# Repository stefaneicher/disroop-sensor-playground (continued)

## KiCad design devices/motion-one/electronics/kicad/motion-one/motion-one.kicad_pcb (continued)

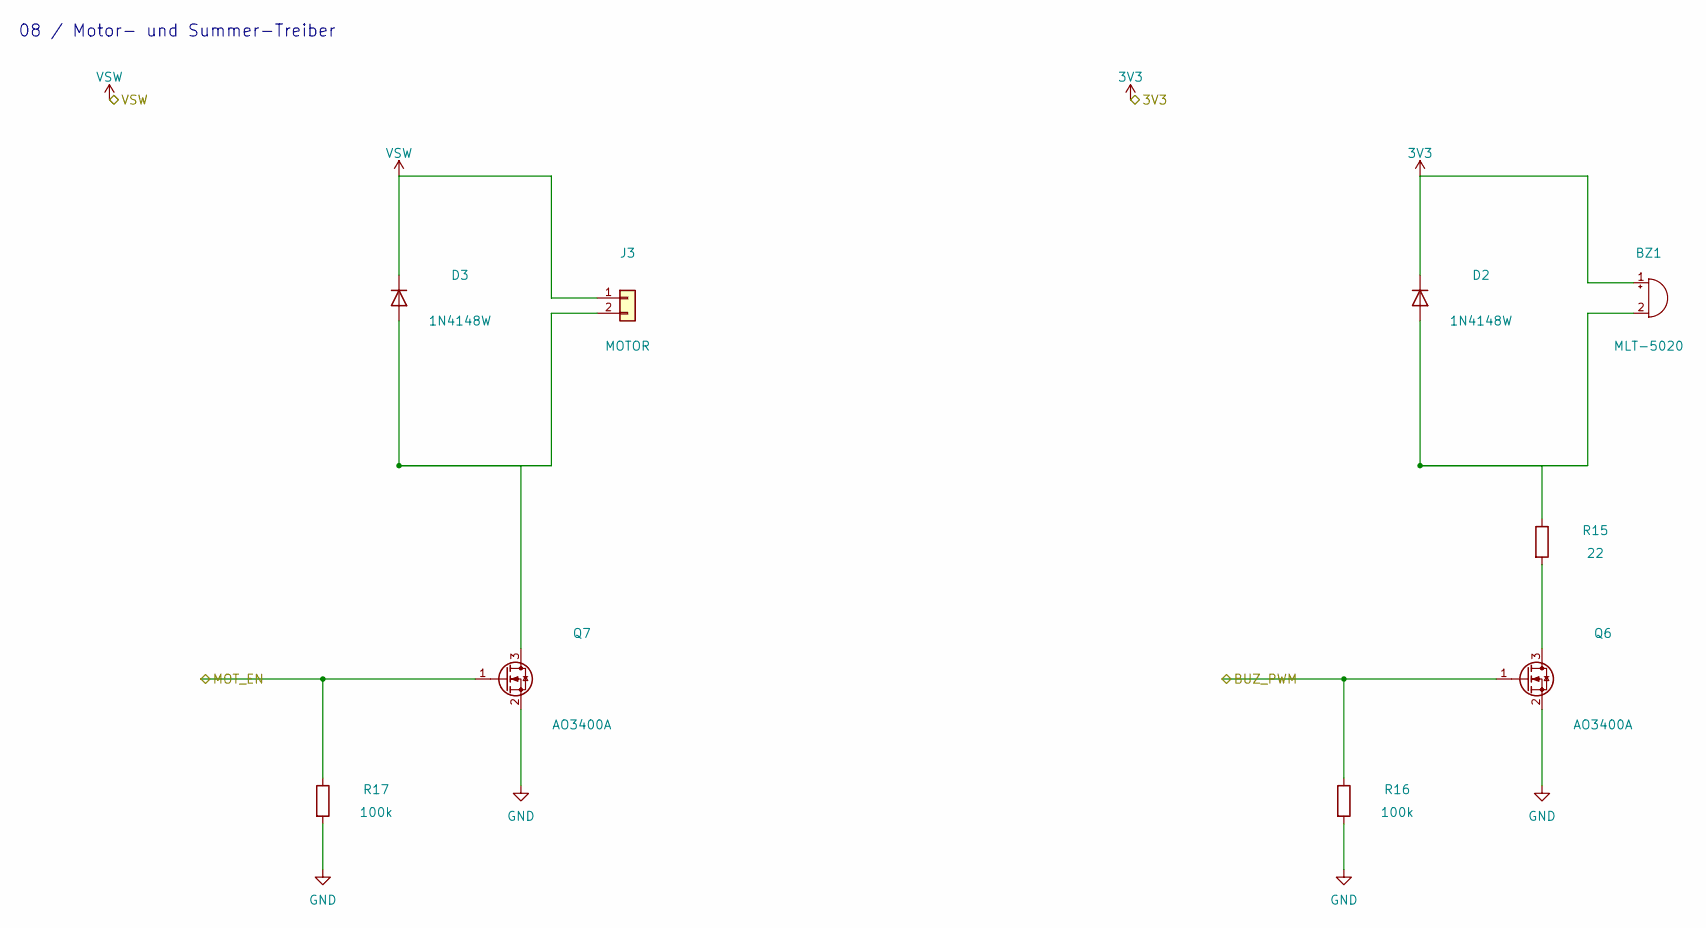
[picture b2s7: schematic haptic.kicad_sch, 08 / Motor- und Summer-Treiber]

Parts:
BZ1: MLT-5020; Buzzer_MLT-5020; LCSC C94598
D2, D3: 1N4148W; D_SOD-123; LCSC C81598
J3: MOTOR; MotorPads_2x1.5
Q6, Q7: AO3400A; SOT-23-3; LCSC C20917
R15: 22; R_1206_3216Metric; LCSC C17958
R16, R17: 100k; R_0402_1005Metric; LCSC C25741

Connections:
3V3: BZ1.1 (+), D2.1 (K); also elsewhere on the board
/haptic/BUZ_PWM: Q6.1 (G), R16.1; also elsewhere on the board
/haptic/MOT_EN: Q7.1 (G), R17.1; also elsewhere on the board
unnamed: BZ1.2 (-), D2.2 (A), R15.1
unnamed: D3.2 (A), J3.2, Q7.3 (D)
unnamed: Q6.3 (D), R15.2
VSW: D3.1 (K), J3.1; also elsewhere on the board

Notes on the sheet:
08 / Motor- und Summer-Treiber

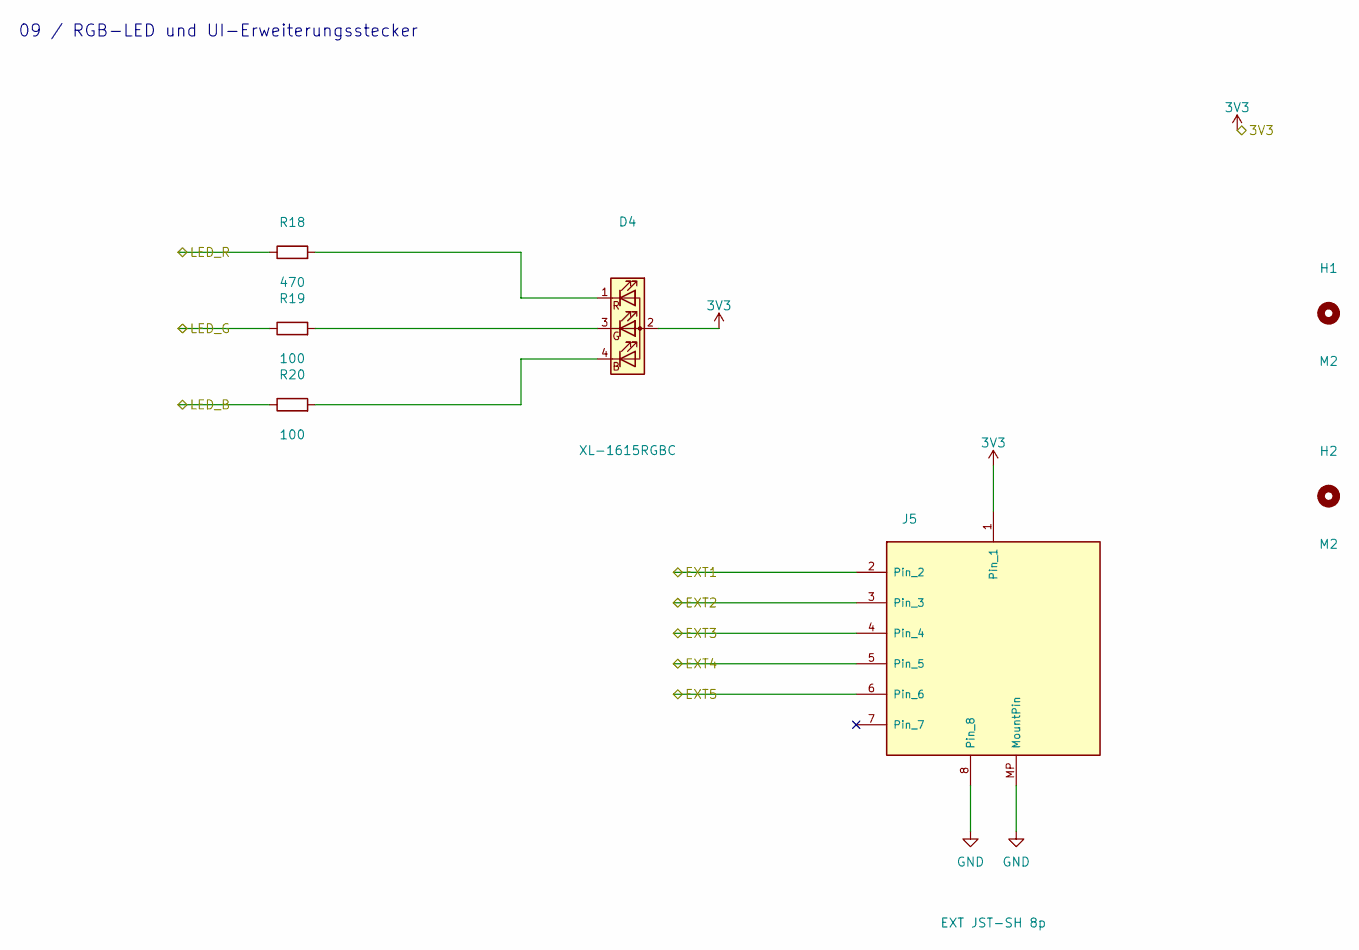
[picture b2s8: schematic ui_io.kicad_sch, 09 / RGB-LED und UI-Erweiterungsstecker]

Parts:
D4: XL-1615RGBC; LED_XL-1615RGBC; LCSC C965840
H1, H2: M2; MountingHole_2.2mm_M2
J5: EXT JST-SH 8p; JST_SH_SM08B-SRSS-TB_1x08-1MP_P1.00mm_Horizontal; LCSC C160407
R18: 470; R_0402_1005Metric; LCSC C25117
R19, R20: 100; R_0402_1005Metric; LCSC C25076

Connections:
3V3: D4.2 (A), J5.1; also elsewhere on the board
/mcu/EXT1: J5.2; also elsewhere on the board
/mcu/EXT2: J5.3; also elsewhere on the board
/mcu/EXT3: J5.4; also elsewhere on the board
/mcu/EXT4: J5.5; also elsewhere on the board
/mcu/EXT5: J5.6; also elsewhere on the board
/mcu/LED_B: R20.1; also elsewhere on the board
/mcu/LED_G: R19.1; also elsewhere on the board
/mcu/LED_R: R18.1; also elsewhere on the board
unnamed: D4.4 (BK), R20.2
unnamed: D4.3 (GK), R19.2
unnamed: D4.1 (RK), R18.2

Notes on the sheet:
09 / RGB-LED und UI-Erweiterungsstecker

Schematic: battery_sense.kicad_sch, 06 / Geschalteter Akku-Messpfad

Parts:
C13: 100nF; C_0402_1005Metric; LCSC C1525
Q4: AO3401A; SOT-23-3; LCSC C15127
Q5: 2N7002; SOT-23-3; LCSC C8545
R11: 1M; R_0402_1005Metric; LCSC C26083
R12, R13, R14: 100k; R_0402_1005Metric; LCSC C25741
TP1: VBAT; TestPoint_Pad_D1.0mm

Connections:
/battery_sense/VBAT_ADC: C13.1, R13.2, R14.1; also elsewhere on the board
/battery_sense/VBAT_EN: Q5.1 (G), R12.1; also elsewhere on the board
unnamed: Q4.3 (D), R13.1
unnamed: Q4.1 (G), Q5.3 (D), R11.2
VBAT: Q4.2 (S), R11.1, TP1.1; also elsewhere on the board

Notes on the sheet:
06 / Geschalteter Akku-Messpfad

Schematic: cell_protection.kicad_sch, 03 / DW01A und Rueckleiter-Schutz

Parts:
C3: 100nF; C_0402_1005Metric; LCSC C1525
Q3: FS8205A; SOT-23-6; LCSC C2830320
R7: 100; R_0402_1005Metric; LCSC C25076
R8: 1k; R_0402_1005Metric; LCSC C11702
U4: DW01A; SOT-23-6; LCSC C351410

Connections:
unnamed: Q3.2 (D), Q3.5 (D)
unnamed: Q3.6 (G1), U4.1 (OD)
unnamed: Q3.4 (G2), U4.3 (OC)
unnamed: R8.1, U4.2 (CS)
VBAT: R7.1; also elsewhere on the board

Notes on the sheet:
03 / DW01A und Rueckleiter-Schutz

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
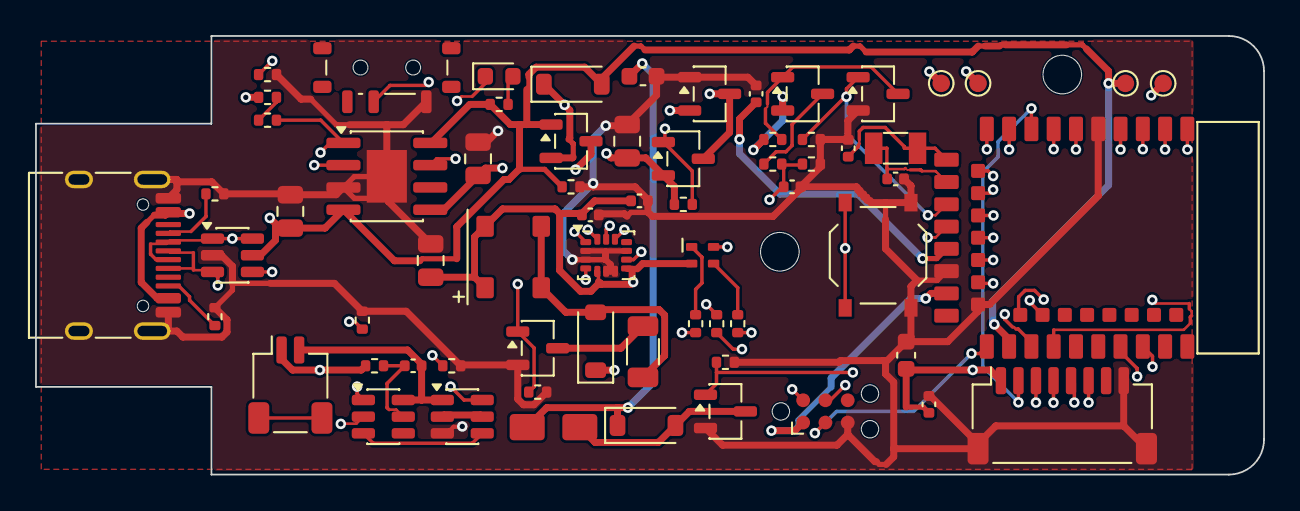
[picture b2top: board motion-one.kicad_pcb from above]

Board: 4 copper layers, 70.0 x 25.0 mm, 68 parts (0 on the bottom side), 54 nets.

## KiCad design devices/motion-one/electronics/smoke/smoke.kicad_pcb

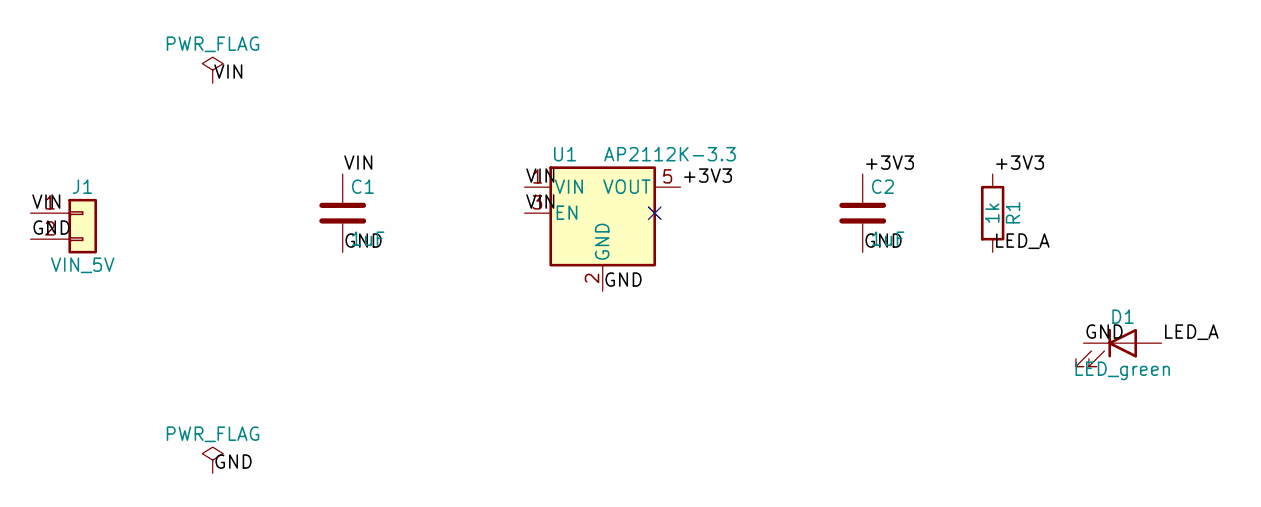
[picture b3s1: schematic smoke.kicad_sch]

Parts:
C1, C2: 1uF; C_0603_1608Metric
D1: LED_green; LED_0603_1608Metric
J1: VIN_5V; PinHeader_1x02_P2.54mm_Vertical
R1: 1k; R_0603_1608Metric
U1: AP2112K-3.3; SOT-23-5

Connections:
/+3V3: C2.1, R1.1, U1.5 (VOUT)
/GND: C1.2, C2.2, D1.1 (K), J1.2, U1.2 (GND)
/LED_A: D1.2 (A), R1.2
/VIN: C1.1, J1.1, U1.1 (VIN), U1.3 (EN)

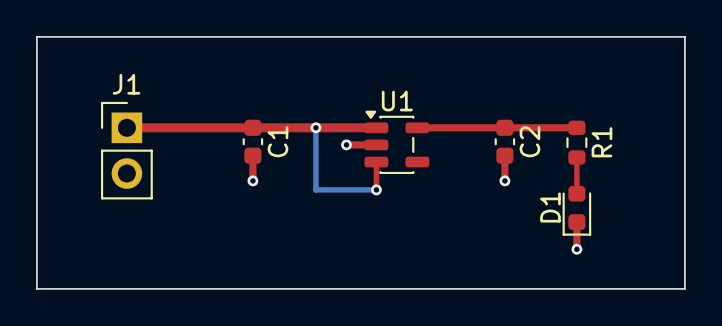
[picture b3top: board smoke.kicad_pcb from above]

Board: 2 copper layers, 36.0 x 14.0 mm, 6 parts (0 on the bottom side), 4 nets.

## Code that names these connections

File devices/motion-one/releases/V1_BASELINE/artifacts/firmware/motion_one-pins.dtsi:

/*
 * EINZIGE Datei mit Pinbelegung fuer Motion One V1.
 * QUELLE: devices/motion-one/electronics/PINOUT_V1.json (revision r4,
 *         sha256 132ac85436ab8b2bb6b5bffa5dbf85fc9524f2b3eff0b1ed6bde9a1ddc3e8e28).
 * Jede Pinzeile traegt ein Tag "PINOUT:<signal>"; firmware/scripts/check_pinout.py
 * gleicht Tag, Port/Pin und Polaritaet gegen PINOUT_V1.json ab (make pincheck).
 * Nicht als GPIO genutzt: XL1/XL2 (32k-Quarz, lfclk), NRESET P0.18 (uicr gpio-as-nreset),
 * VBUS/USB D+/D- (USBD), SWDIO/SWCLK. Kein UART-Pin herausgefuehrt -> uart0 aus.
 */

&pinctrl {
	spi3_default: spi3_default {
		group1 {
			psels = <NRF_PSEL(SPIM_SCK, 0, 6)>,  /* PINOUT:IMU_SCK */
				<NRF_PSEL(SPIM_MOSI, 0, 8)>, /* PINOUT:IMU_MOSI */
				<NRF_PSEL(SPIM_MISO, 1, 9)>; /* PINOUT:IMU_MISO */
		};
	};
	spi3_sleep: spi3_sleep {
		group1 {
			psels = <NRF_PSEL(SPIM_SCK, 0, 6)>, <NRF_PSEL(SPIM_MOSI, 0, 8)>,
				<NRF_PSEL(SPIM_MISO, 1, 9)>;
			low-power-enable;
		};
	};
	/* LEDs Common-Anode an 3V3, aktiv low: nordic,invert -> Ruhepegel high (aus) */
	pwm0_default: pwm0_default {
		group1 {
			psels = <NRF_PSEL(PWM_OUT0, 0, 15)>, /* PINOUT:LED_R */
				<NRF_PSEL(PWM_OUT1, 0, 17)>, /* PINOUT:LED_G */
				<NRF_PSEL(PWM_OUT2, 1, 10)>; /* PINOUT:LED_B */
			nordic,invert;
		};
	};
	pwm0_sleep: pwm0_sleep {
		group1 {
			psels = <NRF_PSEL(PWM_OUT0, 0, 15)>, <NRF_PSEL(PWM_OUT1, 0, 17)>,
				<NRF_PSEL(PWM_OUT2, 1, 10)>;
			low-power-enable;
		};
	};
	pwm1_default: pwm1_default {
		group1 {
			psels = <NRF_PSEL(PWM_OUT0, 0, 2)>; /* PINOUT:BUZ_PWM */
		};
	};
	pwm1_sleep: pwm1_sleep {
		group1 {
			psels = <NRF_PSEL(PWM_OUT0, 0, 2)>;
			low-power-enable;
		};
	};
	/* F-12: Motor per PWM (eigene Instanz, da Summer die Periode von pwm1 aendert) */
	pwm2_default: pwm2_default {
		group1 {
			psels = <NRF_PSEL(PWM_OUT0, 1, 13)>; /* PINOUT:MOT_EN */
		};
	};
	pwm2_sleep: pwm2_sleep {
		group1 {
			psels = <NRF_PSEL(PWM_OUT0, 1, 13)>;
			low-power-enable;
		};
	};
};

&spi3 {
	compatible = "nordic,nrf-spim";
	status = "okay";
	pinctrl-0 = <&spi3_default>;
	pinctrl-1 = <&spi3_sleep>;
	pinctrl-names = "default", "sleep";
	cs-gpios = <&gpio0 12 GPIO_ACTIVE_LOW>; /* PINOUT:IMU_CS (Boot: sofort high, app/src/board_early.c) */

	imu: icm45686@0 {
		compatible = "disroop,icm45686";
		reg = <0>;
		spi-max-frequency = <8000000>; /* PCB-Hinweis: 8 MHz (ICM max. 24 MHz, QUELLE hal_tdk) */
		int1-gpios = <&gpio0 7 GPIO_ACTIVE_HIGH>; /* PINOUT:IMU_INT1 push-pull */
		int2-gpios = <&gpio0 26 GPIO_ACTIVE_HIGH>; /* PINOUT:IMU_INT2 push-pull, derzeit ungenutzt */
	};
};

&pwm0 {
	status = "okay";
	pinctrl-0 = <&pwm0_default>;
	pinctrl-1 = <&pwm0_sleep>;
	pinctrl-names = "default", "sleep";
};

&pwm1 {
	status = "okay";
	pinctrl-0 = <&pwm1_default>;
	pinctrl-1 = <&pwm1_sleep>;
	pinctrl-names = "default", "sleep";
};

&pwm2 {
	status = "okay";
	pinctrl-0 = <&pwm2_default>;
	pinctrl-1 = <&pwm2_sleep>;
	pinctrl-names = "default", "sleep";
};

&uart0 {
	status = "disabled";
};

&adc {
	status = "okay";
	#address-cells = <1>;
	#size-cells = <0>;

	channel@0 {
		reg = <0>;
		zephyr,gain = "ADC_GAIN_1_6";
		zephyr,reference = "ADC_REF_INTERNAL";
		/* Quelle 100k||100k = 50 kOhm -> 40 us (Nordic-Tabelle: 40 us bis 800 kOhm) */
		zephyr,acquisition-time = <ADC_ACQ_TIME(ADC_ACQ_TIME_MICROSECONDS, 40)>;
		zephyr,input-positive = <NRF_SAADC_AIN2>; /* PINOUT:VBAT_ADC */
		zephyr,resolution = <12>;
		zephyr,oversampling = <4>;
	};
	/* J5 EXT1 Stick X (r4), Quelle <= 2.5 kOhm + 100 Ohm -> 10 us */
	channel@1 {
		reg = <1>;
		zephyr,gain = "ADC_GAIN_1_6";
		zephyr,reference = "ADC_REF_INTERNAL";
		zephyr,acquisition-time = <ADC_ACQ_TIME(ADC_ACQ_TIME_MICROSECONDS, 10)>;
		zephyr,input-positive = <NRF_SAADC_AIN5>; /* PINOUT:EXT1 */
		zephyr,resolution = <12>;
	};
	/* J5 EXT2 Stick Y */
	channel@2 {
		reg = <2>;
		zephyr,gain = "ADC_GAIN_1_6";
		zephyr,reference = "ADC_REF_INTERNAL";
		zephyr,acquisition-time = <ADC_ACQ_TIME(ADC_ACQ_TIME_MICROSECONDS, 10)>;
		zephyr,input-positive = <NRF_SAADC_AIN6>; /* PINOUT:EXT2 */
		zephyr,resolution = <12>;
	};
	/* J5 EXT3 frei/analog */
	channel@3 {
		reg = <3>;
		zephyr,gain = "ADC_GAIN_1_6";
		zephyr,reference = "ADC_REF_INTERNAL";
		zephyr,acquisition-time = <ADC_ACQ_TIME(ADC_ACQ_TIME_MICROSECONDS, 10)>;
		zephyr,input-positive = <NRF_SAADC_AIN7>; /* PINOUT:EXT3 */
		zephyr,resolution = <12>;
	};
	/* J5 EXT4 Stick-Taste analog (AIN1), Tag-Pin siehe zephyr,user */
	channel@4 {
		reg = <4>;
		zephyr,gain = "ADC_GAIN_1_6";
		zephyr,reference = "ADC_REF_INTERNAL";
		zephyr,acquisition-time = <ADC_ACQ_TIME(ADC_ACQ_TIME_MICROSECONDS, 10)>;
		zephyr,input-positive = <NRF_SAADC_AIN1>; /* EXT4 AIN1 */
		zephyr,resolution = <12>;
	};
};

/ {
	pwmleds {
		compatible = "pwm-leds";
		led_red: led_red {
			pwms = <&pwm0 0 PWM_MSEC(1) PWM_POLARITY_INVERTED>; /* aktiv low */
		};
		led_green: led_green {
			pwms = <&pwm0 1 PWM_MSEC(1) PWM_POLARITY_INVERTED>; /* aktiv low */
		};
		led_blue: led_blue {
			pwms = <&pwm0 2 PWM_MSEC(1) PWM_POLARITY_INVERTED>; /* aktiv low */
		};
		buzzer: buzzer {
			pwms = <&pwm1 0 PWM_USEC(2273) PWM_POLARITY_NORMAL>; /* FET-Gate, high = an */
		};
		motor: motor {
			/* MOT_EN FET-Gate high = an (100k Pull-down); 20 kHz ANNAHME (unhoerbar) */
			pwms = <&pwm2 0 PWM_USEC(50) PWM_POLARITY_NORMAL>;
		};
	};

	buttons {
		compatible = "gpio-keys";
		button0: button_0 {
			gpios = <&gpio0 28 (GPIO_PULL_UP | GPIO_ACTIVE_LOW)>; /* PINOUT:BTN */
			zephyr,code = <INPUT_KEY_0>;
		};
	};

	zephyr,user {
		io-channels = <&adc 0>, <&adc 1>, <&adc 2>, <&adc 3>, <&adc 4>;
		/* r4 J5: EXT4 Stick-Taste aktiv low mit internem Pull-up; EXT5 Touch TTP233H aktiv high,
		 * Pull-down haelt den Eingang ohne Bedienplatine definiert low (kein Ereignisspam) */
		ext4-gpios = <&gpio0 3 (GPIO_PULL_UP | GPIO_ACTIVE_LOW)>; /* PINOUT:EXT4 */
		ext5-gpios = <&gpio1 11 (GPIO_PULL_DOWN | GPIO_ACTIVE_HIGH)>; /* PINOUT:EXT5 */
		vbat-en-gpios = <&gpio0 5 GPIO_ACTIVE_HIGH>; /* PINOUT:VBAT_EN */
		/* QUELLE PINOUT_V1 notes: VBAT_ADC = VBAT * 100k/(100k+100k) -> Faktor 2 */
		vbat-divider-num = <2>;
		vbat-divider-den = <1>;
	};

	aliases {
		led-red = &led_red;
		led-green = &led_green;
		led-blue = &led_blue;
		buzzer = &buzzer;
		sw0 = &button0;
		motor0 = &motor;
		imu0 = &imu;
	};
};

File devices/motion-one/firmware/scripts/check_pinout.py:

#!/usr/bin/env python3
"""Gleicht electronics/PINOUT_V1.json gegen boards/.../motion_one-pins.dtsi ab.
Jede DTS-Pinzeile traegt '/* PINOUT:<SIGNAL> */'. Exit 0 nur, wenn alle GPIO-Signale aus dem
PINOUT genau einmal getaggt sind, Port/Pin stimmen und Polaritaet/Pull passen."""
import json, re, sys, pathlib

FW = pathlib.Path(__file__).resolve().parents[1]
pinout = pathlib.Path(sys.argv[1]) if len(sys.argv) > 1 else FW.parent / "electronics/PINOUT_V1.json"
dtsi = pathlib.Path(sys.argv[2]) if len(sys.argv) > 2 else FW / "boards/disroop/motion_one/motion_one-pins.dtsi"
# Signale ohne GPIO-Funktion in der App (Hardwarefunktion, siehe dtsi-Kopf)
NON_GPIO = {"XL1", "XL2", "NRESET", "VBUS", "USB_DM", "USB_DP", "SWDIO", "SWCLK"}

data = json.loads(pinout.read_text())
want, ain = {}, {}
for p in data["pins"]:
    m = re.match(r"P([01])\.(\d+)(?:/AIN(\d))?$", p["gpio"])
    if p["signal"] in NON_GPIO:
        continue
    if not m:
        sys.exit(f"FAIL unbekanntes GPIO-Format {p['signal']}: {p['gpio']}")
    want[p["signal"]] = (int(m[1]), int(m[2]))
    if m[3] is not None:
        ain[p["signal"]] = int(m[3])

errs, seen = [], {}
for no, line in enumerate(dtsi.read_text().splitlines(), 1):
    t = re.search(r"PINOUT:(\w+)", line)
    if not t:
        continue
    sig = t[1]
    if sig in seen:
        errs.append(f"{sig}: doppelt getaggt (Zeile {seen[sig]} und {no})")
    seen[sig] = no
    if sig not in want:
        errs.append(f"{sig}: nicht in PINOUT (Zeile {no})"); continue
    m = re.search(r"NRF_PSEL\(\w+,\s*(\d+),\s*(\d+)\)", line) or re.search(r"&gpio(\d)\s+(\d+)", line)
    a = re.search(r"NRF_SAADC_AIN(\d)", line)
    if m:
        got = (int(m[1]), int(m[2]))
        if got != want[sig]:
            errs.append(f"{sig}: DTS P{got[0]}.{got[1]} != PINOUT P{want[sig][0]}.{want[sig][1]} (Zeile {no})")
    elif a:
        if ain.get(sig) != int(a[1]):
            errs.append(f"{sig}: DTS AIN{a[1]} != PINOUT AIN{ain.get(sig)} (Zeile {no})")
    else:
        errs.append(f"{sig}: kein Pin in Zeile {no}")
for sig in sorted(set(want) - set(seen)):
    errs.append(f"{sig}: im PINOUT, aber nicht in DTS")

text = dtsi.read_text()
func = {p["signal"]: p["function"].lower() for p in data["pins"]}
# Polaritaet/Pull aus PINOUT-Funktionstext
for led in ("LED_R", "LED_G", "LED_B"):
    if "aktiv low" in func.get(led, "") or any("led aktiv low" in n.lower() for n in data.get("notes", [])):
        if text.count("PWM_POLARITY_INVERTED") < 3 or "nordic,invert" not in text:
            errs.append(f"{led}: aktiv low, DTS nicht invertiert"); break
if "pull-up" in func.get("BTN", "") and not re.search(r"GPIO_PULL_UP \| GPIO_ACTIVE_LOW\)>;\s*/\* PINOUT:BTN", text):
    errs.append("BTN: interner Pull-up/aktiv low fehlt")
if "aktiv low" in func.get("IMU_CS", "") and not re.search(r"cs-gpios.*GPIO_ACTIVE_LOW.*PINOUT:IMU_CS", text):
    errs.append("IMU_CS: nicht aktiv low")
if "spi-max-frequency = <8000000>" not in text:
    errs.append("SPI nicht 8 MHz")
m = re.search(r"VBAT\s*\*\s*(\d+)k/\((\d+)k\+(\d+)k\)", " ".join(data.get("notes", [])))
if m:
    num, den = int(m[2]) + int(m[3]), int(m[1])
    dn = re.search(r"vbat-divider-num = <(\d+)>", text); dd = re.search(r"vbat-divider-den = <(\d+)>", text)
    if not (dn and dd and int(dn[1]) * den == int(dd[1]) * num):
        errs.append(f"VBAT-Teiler != {num}/{den}")

print(f"PINOUT {pinout.name} revision {data.get('revision')}: {len(want)} GPIO-Signale, {len(seen)} DTS-Tags")
for e in errs:
    print("FAIL", e)
print("pincheck", "FAIL" if errs else "PASS")
sys.exit(1 if errs else 0)
